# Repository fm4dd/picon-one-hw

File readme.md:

## PiCon-One

### Description

PiCon-One is a multi-function controller for automation and industrial use cases.
At its heart is the smallest member of the Raspberry family, the Raspberry Pi Zero W.
Instead of adding a "hat" on top of the Raspberry, I reversed the roles:
The Pi becomes the "hat" for the controller mainboard, which has been fitted to 
a Takachi enclosure.

The design aims to add flexible power configuration, real-time clock, GPS positioning,
display and communication interfaces, enabling rapid prototyping under the widespread
Raspberry Pi ecosystem.

### Schematic
[PiCon-One Schematics](picon-one-schematics-v10a.pdf)

### PCB Gerber

Layers: 2
Dimension: 118mm x 168mm
PCB Thickness: 1.6
PCB Color: Green
Surface Finish: LeadFree HASL-RoHS
Copper Weight: 1
Material: FR4-Standard Tg 130-140C
Gerber: [PiCon-One Gerber V1.0a](picon-one-gerber-v10a.zip)

### Components Layout

Takachi Enclosure: SPCP131805T, 125mm x 175mm x 50mm

### Bill of Materials

[BOM file PiCon-One v1.0a](./picon-one-bom-v10a.csv)

### Assembly

SMT parts assembly has been combined with PCB manufacturing. 
Remaining is the THT parts assembly.

#### Software and Drivers

Example software and setup is kept in a separate github repo at
https://github.com/fm4dd/picon-one-sw

### License

CERN Open Hardware Licence v1.2

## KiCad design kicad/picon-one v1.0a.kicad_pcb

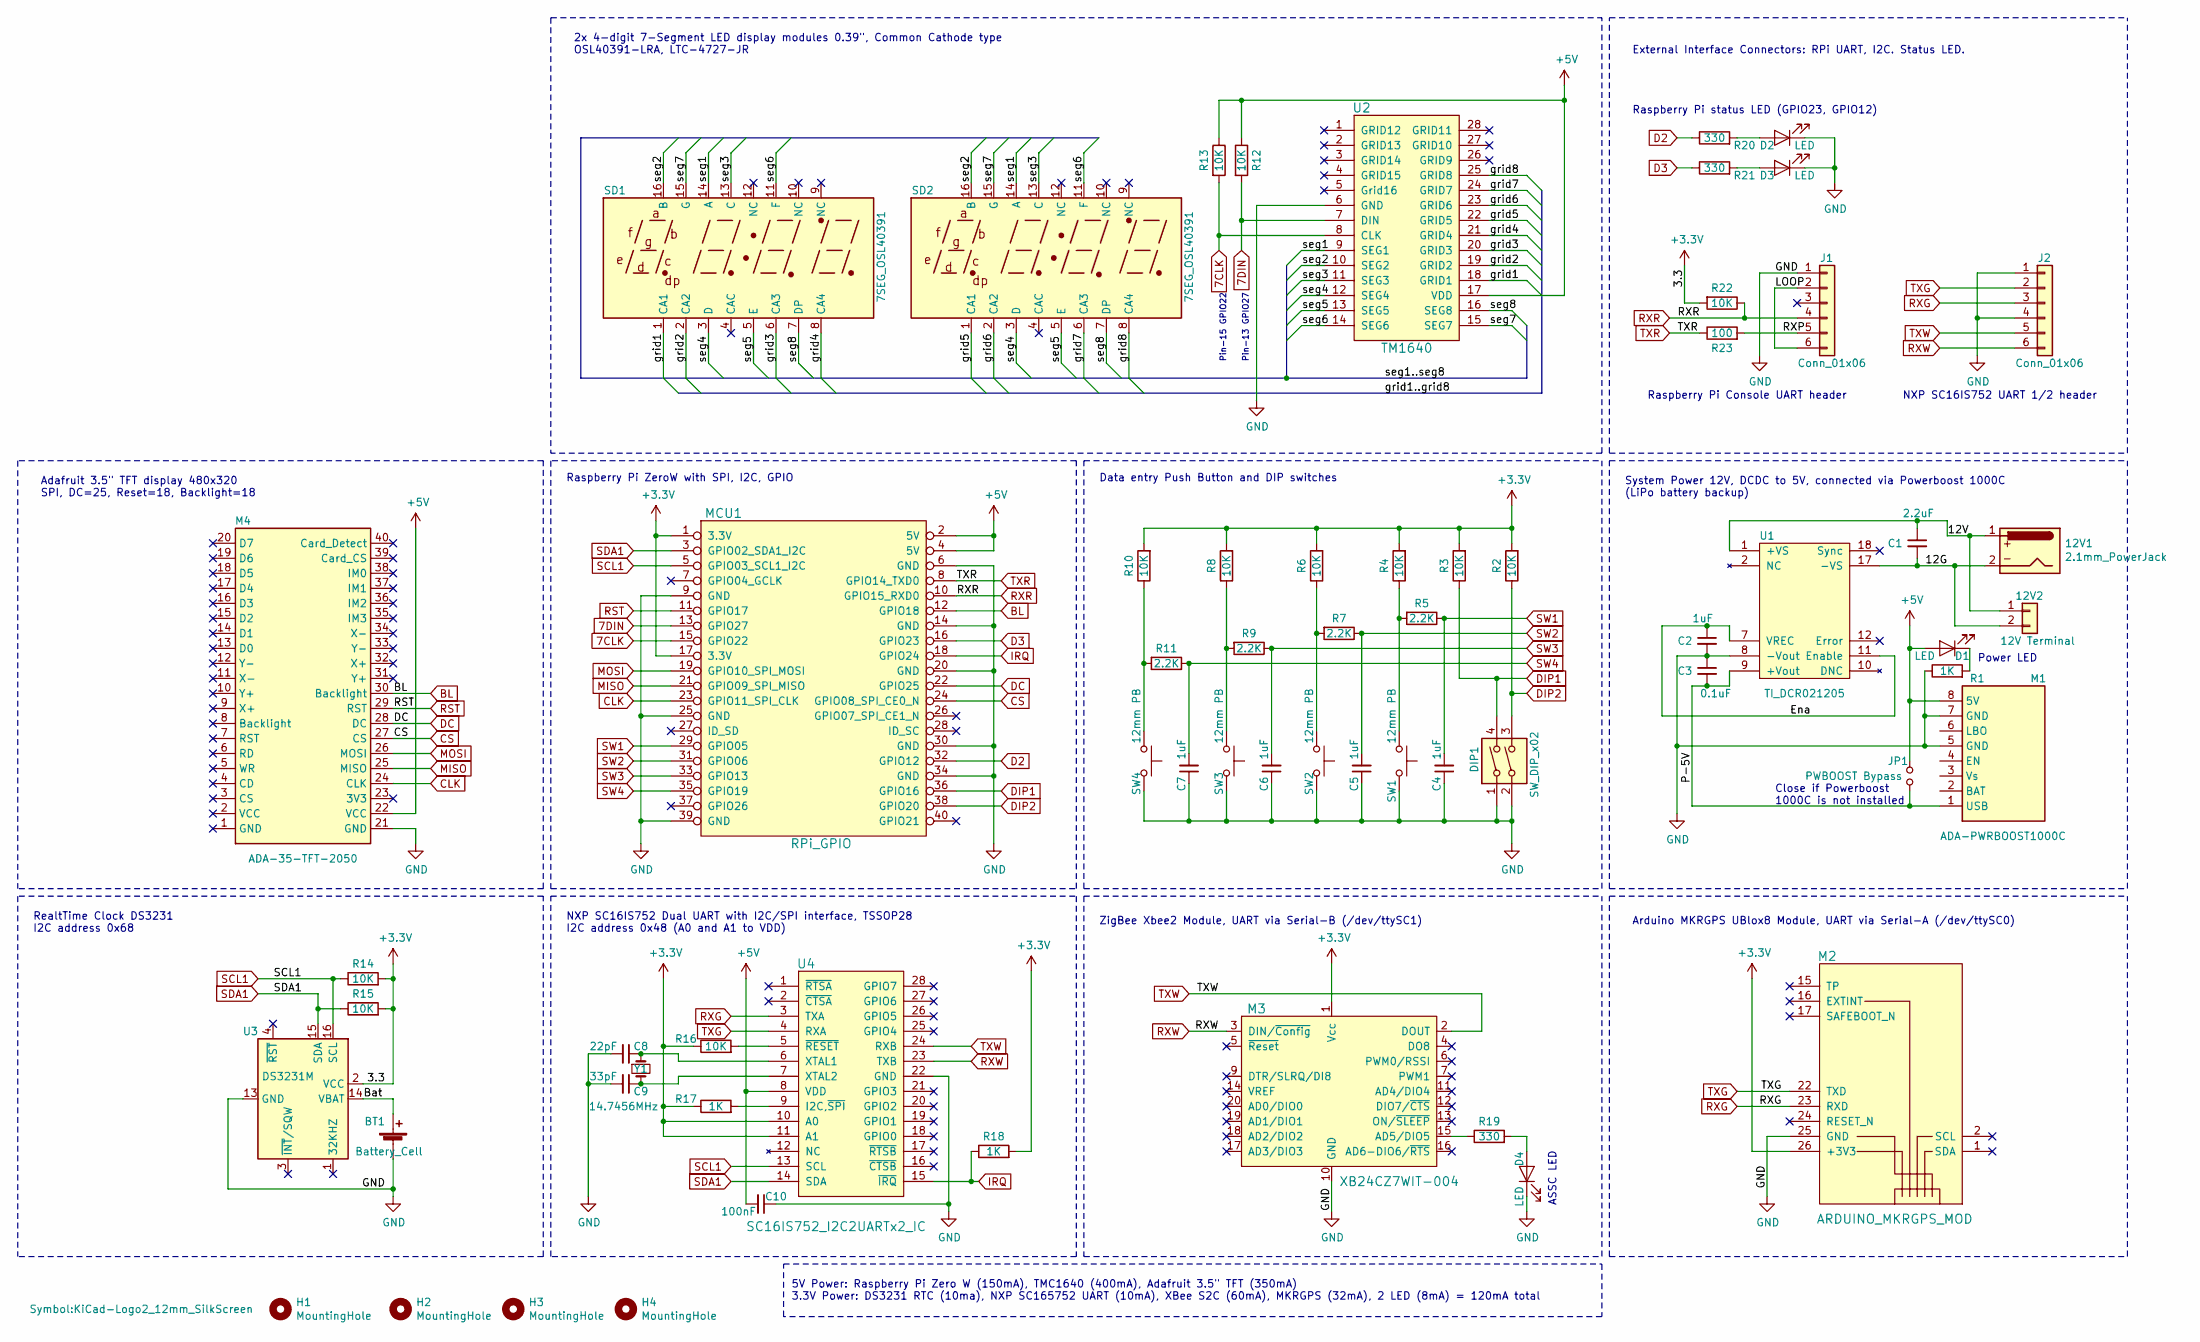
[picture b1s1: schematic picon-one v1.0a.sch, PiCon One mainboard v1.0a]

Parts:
12V1: 2.1mm_PowerJack; BarrelJack_2.1mm
12V2: 12V Terminal; TerminalBlock_Phoenix_MKDS-1,5-2-5.08_1x02_P5.08mm_Horizont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
BT1: Battery_Cell; BatteryHolder_LINX_BAT-HLD-012-SMT
C1: 2.2uF; C_Disc_D3.0mm_W1.6mm_P2.50mm
C2, C4, C5, C6, C7: 1uF; C_Disc_D3.0mm_W1.6mm_P2.50mm
C3: 0.1uF; C_Disc_D3.0mm_W1.6mm_P2.50mm
C8: 22pF; C_0805_2012Metric_Pad1.15x1.40mm_HandSolder
C9: 33pF; C_0805_2012Metric_Pad1.15x1.40mm_HandSolder
C10: 100nF; C_0805_2012Metric_Pad1.15x1.40mm_HandSolder
D1, D2, D3, D4: LED; LED_D3.0mm
DIP1: SW_DIP_x02; SW_DIP_SPSTx02_Slide_9.78x7.26mm_W7.62mm_P2.54mm
H1, H2, H3, H4: MountingHole; MountingHole_3.2mm_M3
J1, J2: Conn_01x06; PinHeader_1x06_P2.54mm_Vertical
JP1: PWBOOST Bypass; PinHeader_1x02_P2.54mm_Vertical
L1: Logo_KiCad; KiCad-Logo2_12mm_SilkScreen
M1: ADA-PWRBOOST1000C
M2: ARDUINO_MKRGPS_MOD; Arduino_MKRGPS
M3: XB24CZ7WIT-004; XBEE-20_THT; MPN XB24CZ7WIT-004; Digi-Key_PN 602-1560-ND
M4: ADA-35-TFT-2050; ADA-35-TFT-2050-no-ears
MCU1: RPi_GPIO; RasPi0_FaceDown
R1: 1K; R_Axial_DIN0204_L3.6mm_D1.6mm_P5.08mm_Horizontal
R2, R3, R4, R6, R8, R10, R12, R13, R14, R15, R22: 10K; R_Axial_DIN0204_L3.6mm_D1.6mm_P5.08mm_Horizontal
R5, R7, R9, R11: 2.2K; R_Axial_DIN0204_L3.6mm_D1.6mm_P5.08mm_Horizontal
R16: 10K; R_0805_2012Metric_Pad1.15x1.40mm_HandSolder
R17, R18: 1K; R_0805_2012Metric_Pad1.15x1.40mm_HandSolder
R19, R20, R21: 330; R_Axial_DIN0204_L3.6mm_D1.6mm_P5.08mm_Horizontal
R23: 100; R_Axial_DIN0204_L3.6mm_D1.6mm_P5.08mm_Horizontal
SD1, SD2: 7SEG_OSL40391; 7SEG-OSL40391
SW1, SW2, SW3, SW4: 12mm PB; SW_PUSH-12mm
U1: TI_DCR021205; TI_DCR01
U2: TM1640; SOP-28_7.5x17.9mm_P1.27mm
U3: DS3231M; SOIC-16W_7.5x10.3mm_P1.27mm
U4: SC16IS752_I2C2UARTx2_IC; TSSOP-28_4.4x9.7mm_P0.65mm
Y1: 14.7456MHz; Crystal_HC49-4H_Vertical

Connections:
7CLK: MCU1.15 (GPIO22), R13.2, U2.8 (CLK)
7DIN: MCU1.13 (GPIO27), R12.2, U2.7 (DIN)
+3V3: M2.26 (+3V3), M3.1 (Vcc), MCU1.1 (3.3V), MCU1.17 (3.3V), R2.2, R3.2, R4.2, R6.2, R8.2, R10.2, R14.2, R15.2, R16.1, R17.1, R18.2, R22.2, U3.2 (VCC), U4.10 (A0), U4.11 (A1)
+5V: C10.2, D1.2 (A), JP1.2, M1.8 (5V), M4.22 (VCC), MCU1.2 (5V), MCU1.4 (5V), R12.1, R13.1, U2.17 (VDD), U4.8 (VDD)
/12G: 12V1.2, 12V2.2, C1.2, U1.17 (-VS)
/12V: 12V1.1, 12V2.1, C1.1, U1.1 (+VS)
/Bat: BT1.1 (+), U3.14 (VBAT)
/Ena: C2.1, U1.7 (VREC), U1.11 (Enable)
/LOOP: J1.2, J1.6
/P-5V: C3.2, JP1.1, M1.1 (USB), U1.9 (+Vout)
/RXP: J1.5, R23.2
/grid1: SD1.1 (CA1), U2.18 (GRID1)
/grid2: SD1.2 (CA2), U2.19 (GRID2)
/grid3: SD1.6 (CA3), U2.20 (GRID3)
/grid4: SD1.8 (CA4), U2.21 (GRID4)
/grid5: SD2.1 (CA1), U2.22 (GRID5)
/grid6: SD2.2 (CA2), U2.23 (GRID6)
/grid7: SD2.6 (CA3), U2.24 (GRID7)
/grid8: SD2.8 (CA4), U2.25 (GRID8)
/seg1: SD1.14 (A), SD2.14 (A), U2.9 (SEG1)
/seg2: SD1.16 (B), SD2.16 (B), U2.10 (SEG2)
/seg3: SD1.13 (C), SD2.13 (C), U2.11 (SEG3)
/seg4: SD1.3 (D), SD2.3 (D), U2.12 (SEG4)
/seg5: SD1.5 (E), SD2.5 (E), U2.13 (SEG5)
/seg6: SD1.11 (F), SD2.11 (F), U2.14 (SEG6)
/seg7: SD1.15 (G), SD2.15 (G), U2.15 (SEG7)
/seg8: SD1.7 (DP), SD2.7 (DP), U2.16 (SEG8)
BL: M4.30 (Backlight), MCU1.12 (GPIO18)
CLK: M4.24 (CLK), MCU1.23 (GPIO11_SPI_CLK)
CS: M4.27 (CS), MCU1.24 (GPIO08_SPI_CE0_N)
D2: MCU1.32 (GPIO12), R20.1
D3: MCU1.16 (GPIO23), R21.1
DC: M4.28 (DC), MCU1.22 (GPIO25)
DIP1: DIP1.4, MCU1.36 (GPIO16), R3.1
DIP2: DIP1.3, MCU1.38 (GPIO20), R2.1
GND: BT1.2 (-), C2.2, C3.1, C4.1, C5.1, C6.1, C7.1, C8.2, C9.2, C10.1, D2.1 (K), D3.1 (K), D4.1 (K), DIP1.1, DIP1.2, J1.1, J2.1, J2.4, M1.5 (GND), M1.7 (GND), M2.25 (GND), M3.10 (GND), M4.21 (GND), MCU1.6 (GND), MCU1.9 (GND), MCU1.14 (GND), MCU1.20 (GND), MCU1.25 (GND), MCU1.30 (GND), MCU1.34 (GND), MCU1.39 (GND), R1.1, SW1.2, SW2.2, SW3.2, SW4.2, U1.8 (-Vout), U2.6 (GND), U3.5 (GND), U3.6 (GND), U3.7 (GND), U3.8 (GND), U3.9 (GND), U3.10 (GND), U3.11 (GND), U3.12 (GND), U3.13 (GND), U4.22 (GND)
IRQ: MCU1.18 (GPIO24), R18.1, U4.15 (~IRQ)
MISO: M4.25 (MISO), MCU1.21 (GPIO09_SPI_MISO)
MOSI: M4.26 (MOSI), MCU1.19 (GPIO10_SPI_MOSI)
unnamed: C8.1, U4.6 (XTAL1), Y1.1
unnamed: C9.1, U4.7 (XTAL2), Y1.2
unnamed: D1.1 (K), R1.2
unnamed: D2.2 (A), R20.2
unnamed: D3.2 (A), R21.2
unnamed: D4.2 (A), R19.2
unnamed: M3.15 (AD5/DIO5), R19.1
unnamed: R4.1, R5.2, SW1.1
unnamed: R6.1, R7.2, SW2.1
unnamed: R8.1, R9.2, SW3.1
unnamed: R10.1, R11.2, SW4.1
unnamed: R16.2, U4.5 (~RESET)
unnamed: R17.2, U4.9 (I2C,~SPI)
RST: M4.29 (RST), MCU1.11 (GPIO17)
RXG: J2.3, M2.23 (RXD), U4.3 (TXA)
RXR: J1.4, MCU1.10 (GPIO15_RXD0), R22.1
RXW: J2.6, M3.3 (DIN/~Config), U4.23 (TXB)
SCL1: MCU1.5 (GPIO03_SCL1_I2C), R14.1, U3.16 (SCL), U4.13 (SCL)
SDA1: MCU1.3 (GPIO02_SDA1_I2C), R15.1, U3.15 (SDA), U4.14 (SDA)
SW1: C4.2, MCU1.29 (GPIO05), R5.1
SW2: C5.2, MCU1.31 (GPIO06), R7.1
SW3: C6.2, MCU1.33 (GPIO13), R9.1
SW4: C7.2, MCU1.35 (GPIO19), R11.1
TXG: J2.2, M2.22 (TXD), U4.4 (RXA)
TXR: MCU1.8 (GPIO14_TXD0), R23.1
TXW: J2.5, M3.2 (DOUT), U4.24 (RXB)

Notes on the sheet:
RealtTime Clock DS3231 I2C address 0x68
Adafruit 3.5" TFT display 480x320 SPI, DC=25, Reset=18, Backlight=18
Raspberry Pi ZeroW with SPI, I2C, GPIO
NXP SC16IS752 Dual UART with I2C/SPI interface, TSSOP28 I2C address 0x48 (A0 and A1 to VDD)
ZigBee Xbee2 Module, UART via Serial-B (/dev/ttySC1)
Data entry Push Button and DIP switches
Arduino MKRGPS UBlox8 Module, UART via Serial-A (/dev/ttySC0)
System Power 12V, DCDC to 5V, connected via Powerboost 1000C (LiPo battery backup)
External Interface Connectors: RPi UART, I2C. Status LED.
2x 4-digit 7-Segment LED display modules 0.39", Common Cathode type OSL40391-LRA, LTC-4727-JR
Close if Powerboost 1000C is not installed
Raspberry Pi Console UART header
Raspberry Pi status LED (GPIO23, GPIO12)
5V Power: Raspberry Pi Zero W (150mA), TMC1640 (400mA), Adafruit 3.5" TFT (350mA) 3.3V Power: DS3231 RTC (10ma), NXP SC165752 UART (10mA), XBee S2C (60mA), MKRGPS (32mA), 2 LED (8mA) = 120mA total
Power LED
ASSC LED
NXP SC16IS752 UART 1/2 header
Pin-15 GPIO22
Pin-13 GPIO27

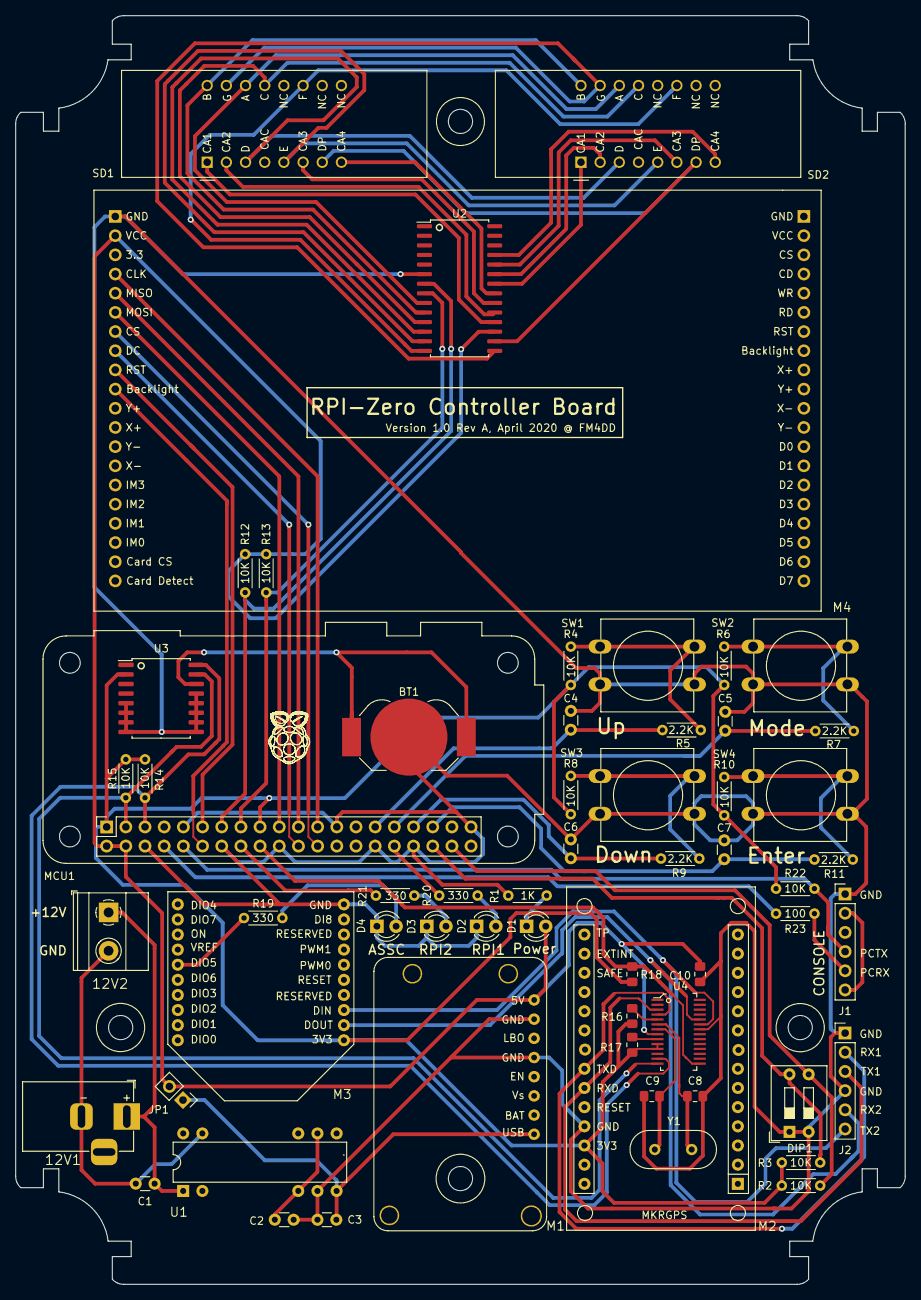
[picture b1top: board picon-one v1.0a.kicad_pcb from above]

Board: 2 copper layers, 117.8 x 168.0 mm, 65 parts (1 on the bottom side), 65 nets.

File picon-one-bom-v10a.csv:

Item,Qty,Reference,Part Description,Type,Manufacturer,Manufacturer Part-#,Distributor,Distributor Part-#
1,1,D2,LED Green Diffused 3mm round,THT,Wurth Electronics Inc.,151031VS06000,Digi-Key,732-5008-ND
2,1,D3,LED Yellow Diffused 3mm round,THT,Wurth Electronics Inc.,151031YS06000,Digi-Key,732-5010-ND
3,1,R20,RES 330 OHM 1/4W 1% AXIAL,THT,Stackpole Electronics Inc,RNMF14FTC330R,Digi-Key,S330CACT-ND
4,1,R21,RES 220 OHM 1/4W 1% AXIAL,THT,Stackpole Electronics Inc,RNMF14FTC220R,Digi-Key,S220CACT-ND
5,1,R22,RES 10K OHM 1/4W 1% AXIAL,THT,Stackpole Electronics Inc,RNMF14FTC10K0,Digi-Key,S10KCACT-ND
6,1,R23,RES 100 OHM 1/4W 1% AXIAL,THT,Stackpole Electronics Inc,RNMF14FTC100R,Digi-Key,S100CACT-ND
7,2,"J1, J2",2x 2.54-pin x6 header for serial pinout,THT,N/A,N/A,Digi-Key,N/A
,,,,,,,,
Item,Qty,Reference,Part Description,Type,Manufacturer,Manufacturer Part-#,Distributor,Distributor Part-#
8,1,12V1,Barrel Jack Connector 2.1mm,THT,CUI Inc.,PJ-002A,Digi-Key,CP-002A-ND
9,1,12V2,TERM BLK 2P SIDE ENT 5.08MM PCB,THT, On Shore Technology Inc.,OSTTC022162,Digi-Key,ED2609-ND
10,1,U1,DC DC CONVERTER 5V 2W,THT,Texas Instruments,DCR021205P,Digi-Key,296-36927-5-ND
11,1,C1,CAP CER 2.2pF 50V C0G Radial,THT,TDK,FG28C0G1H2R2CNT06,Digi-Key,445-173491-1-ND
12,1,C2,CAP CER 1UF 50V X8L Radial,THT,KEMET,C320C105K5N5TA91707301,Digi-Key,399-14394-1-ND
13,1,C3,CAP CER 0.1UF 50V X7R RADIAL,THT,AVX,SR215C104KAT,Digi-Key,SR215C104KAT-ND
14,1,R1,RES 1K OHM 1/4W 1% AXIAL,THT,Stackpole Electronics Inc,RNMF14FTC1K0,Digi-Key,S1KCACT-ND
15,1,D1,LED Red Diffused 3mm round,THT,Wurth Electronics Inc.,151031SS04000,Digi-Key,732-5005-ND
16,1,M1,PWRBOOST 1000 5V LIPO USB,THT,Adafruit Industries LLC,2465,Digi-Key,1528-1349-ND
17,1,JP1,2x 2.54-pin header and Jumper,THT,,,Digi-Key,
,,,,,,,,
Item,Qty,Reference,Part Description,Type,Manufacturer,Manufacturer Part-#,Distributor,Distributor Part-#
18,1,M2,Arduino MKR GPS Shield,THT,Arduino,ASX00017,Digi-Key,1050-1171-ND
,,,,,,,,
Item,Qty,Reference,Part Description,Type,Manufacturer,Manufacturer Part-#,Distributor,Distributor Part-#
19,2,"DS1, DS2",0.39 Inch 4-Digit 7-Segment Display,THT,OptoSupply,OSL40391-LRA,Akizuki,I-09971
20,1,U2,TM1640 LED driver IC,SMT,Titan Microelectronics,TM1640,LCSC,C41327
21,2,"R12, R13",RES 10K OHM 1/4W 1% AXIAL,THT,Stackpole Electronics Inc,RNMF14FTC10K0,Digi-Key,S10KCACT-ND
,,,,,,,,
Item,Qty,Reference,Part Description,Type,Manufacturer,Manufacturer Part-#,Distributor,Distributor Part-#
22,1,DIP1," DIP SWITCH, SPST, 2.54 PITCH, RA",THT,CUI Devices, DS01-254-S-02BE,Digi-Key, 2223-DS01-254-S-02BE-ND
23,4,SW1-SW4,12mm SWITCH TACTILE SPST-NO 0.05A 24V,THT,TE Connectivity, FSM103,Digi-Key, 450-1158-ND
24,4,"C4, C5, C6, C7",CAP CER 1UF 50V X8L Radial,THT,KEMET,C320C105K5N5TA91707301,Digi-Key,399-14394-1-ND
25,6,"R2-4, R6, R8, R10",RES 10K OHM 1/4W 1% AXIAL,THT,Stackpole Electronics Inc,RNMF14FTC10K0,Digi-Key,S10KCACT-ND
26,4,"R5, R7, R9, R11",RES 2K2 OHM 1/4W 1% AXIAL,THT,Stackpole Electronics Inc,RNMF14FAD2K20,Digi-Key,RNMF14FAD2K20CT-ND
,,,,,,,,
Item,Qty,Reference,Part Description,Type,Manufacturer,Manufacturer Part-#,Distributor,Distributor Part-#
27,1,M3,Xbee RF TXRX Module S2C,THT,Digi International,XB24CZ7PIT-004,Digi-Key,602-1557-ND
28,1,R19,RES 330 OHM 1/4W 1% AXIAL,THT,Stackpole Electronics Inc,RNMF14FTC330R,Digi-Key,S330CACT-ND
29,1,D4,LED Red Diffused 3mm round,THT,Wurth Electronics Inc.,151031SS04000,Digi-Key,732-5005-ND
,,,,,,,,
Item,Qty,Reference,Part Description,Type,Manufacturer,Manufacturer Part-#,Distributor,Distributor Part-#
30,1,MCU1,Raspberry Pi Zero W BCM2835,NA,Pi Supply,RPI-027,Digi-Key,1910-1000-ND
31,1,N/A,CONN RCPT 40POS 0.1 TIN PCB,THT,Harwin Inc.,M20-7832046,Digi-Key,952-2150-ND
32,4,N/A,BOARD SUPRT SNAP LOCK NYLON 11MM,NA,Wrth Elektronik,709670110,Digi-Key,732-10378-ND
,,,,,,,,
Item,Qty,Reference,Part Description,Type,Manufacturer,Manufacturer Part-#,Distributor,Distributor Part-#
33,1,M4,"3.5"" TFT 320X480 Touchscreen",THT,Adafruit Industries LLC,2050,Digi-Key,1528-1470-ND
34,1,N/A,40-pin Socket 2.54mm single row,THT,"Neltron Industrial Co., Ltd.",6604-S,Akizuki,P-01591
35,2,N/A,"2.54mm Pin Header Strip, Straight, Single Row",THT,"Useconn Electronics, Ltd",PHA-1x40SG-XX,Akizuki,C-06637
,,,,,,,,
Item,Qty,Reference,Part Description,Type,Manufacturer,Manufacturer Part-#,Distributor,Distributor Part-#
36,1,U3,DS3231 I2C Real Time Clock IC,SMT,Maxim Integrated,DS3231M+TRL,LCSC,C37663
37,1,BT1,BATTERY RETAINER COIN 12MM SMD,SMT,Linx Technologies Inc.,BAT-HLD-012-SMT,Digi-Key,BAT-HLD-012-SMT-ND
38,2,"R14, R15",RES 10K OHM 1/4W 1% AXIAL,THT,Stackpole Electronics Inc,RNMF14FTC10K0,Digi-Key,S10KCACT-ND
,,,,,,,,
Item,Qty,Reference,Part Description,Type,Manufacturer,Manufacturer Part-#,Distributor,Distributor Part-#
39,1,N/A,SPCP IP67 POLYCARBONATE ENCLOSURE,NA,Takachi,SPCP131805T,Amazon,N/A
40,4,N/A,MACH SCREW BINDING HEAD COMBO M4,NA,Keystone Electronics,7799-1,Digi-Key,36-7799-1-ND
,,,,,,,,
Item,Qty,Reference,Part Description,Type,Manufacturer,Manufacturer Part-#,Distributor,Distributor Part-#
41,1,U4,SC16IS752 Dual UART IC,SMT,NXP,"SC16IS752IPW,128",Digi-Key,568-11944-1-ND
42,1,Y1,CRYSTAL 14.74560MHZ 30PF,THT,IQD Frequency Products,LFXTAL003224BULK,Digi-Key,1923-1432-ND
43,1,C8,CAP 22pF 10% 50V X7R C_0805,SMT,Samsung,CL21C220JBANNNC,LCSC,C1804
44,1,C9,CAP 33pF 5% 50V C_0805,SMT,Samsung,CL21C330JBANNNC,LCSC,C1814
45,1,C10,CAP 100nF 5% 50V X7R C_0805,SMT,Samsung,CL21B104JBCNNNC,LCSC,C62912
46,1,R16,RES 10K OHM 1% R_0805,SMT,Uniroyal Elec,0805W8F1002T5E,LCSC,C17414
47,2,"R17,R18",RES 1K OHM 1% R_0805,SMT,Uniroyal Elec,0805W8F1001T5E,LCSC,C17513

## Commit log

2020-05-24 Repo Init
2020-05-31 1st repo upload
